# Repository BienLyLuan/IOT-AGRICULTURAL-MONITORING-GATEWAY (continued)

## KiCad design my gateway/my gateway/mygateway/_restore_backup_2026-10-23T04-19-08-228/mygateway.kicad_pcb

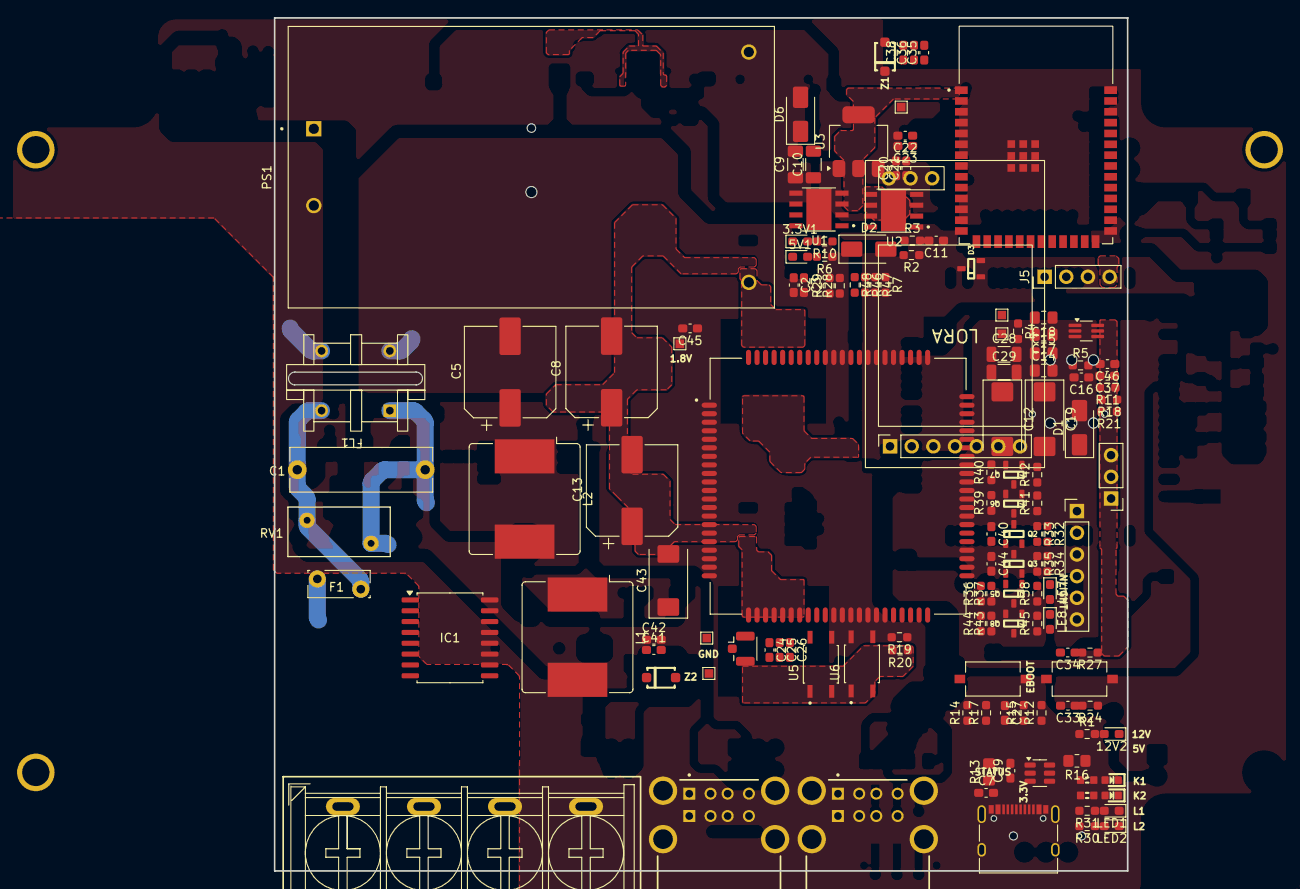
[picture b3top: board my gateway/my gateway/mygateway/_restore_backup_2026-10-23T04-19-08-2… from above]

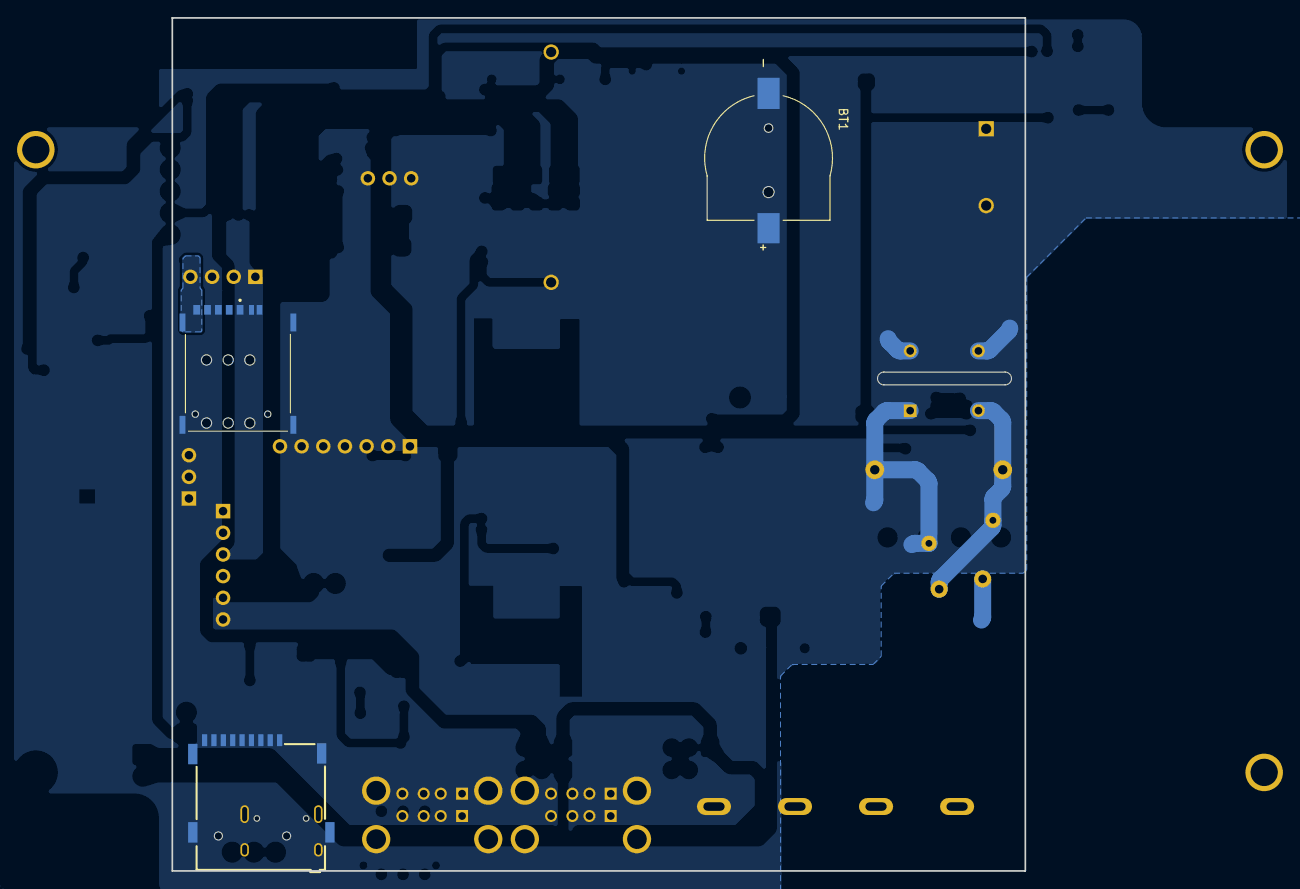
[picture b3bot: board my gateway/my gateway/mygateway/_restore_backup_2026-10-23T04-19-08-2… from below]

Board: 2 copper layers, 100.0 x 100.0 mm, 145 parts (3 on the bottom side), 84 nets.

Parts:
1.8V1, 3.3v2, 4v1, 5v2, 12v1: TestPoint; TestPoint_Pad_1.0x1.0mm
3.3V1, 12V2: Led_red; LED_0603_1608Metric_Pad1.05x0.95mm_HandSolder
5V1: led_red; LED_0603_1608Metric_Pad1.05x0.95mm_HandSolder
BT1: CR1220; MPD_BC501SM-TR
C1: 0.1uF/275VAC; C_Rect_L16.5mm_W5.0mm_P15.00mm_MKT
C2, C7, C21, C22, C25, C33, C35, C39, C42: 10uF/0603; C_0603_1608Metric_Pad1.08x0.95mm_HandSolder
C3, C20, C23, C26, C34, C36, C40, C41, C44, C45, C46: 100nF/0603; C_0603_1608Metric_Pad1.08x0.95mm_HandSolder
C5: 470uF/10x10.5/35V; CP_Elec_10x10.5
C8, C13: 470uF/35V/10x10.5; CP_Elec_10x10.5
C9: 10uF/0805/50V; C_1206_3216Metric_Pad1.33x1.80mm_HandSolder
C10: 100nF/0805/50V; C_1206_3216Metric_Pad1.33x1.80mm_HandSolder
C11, C16: 10nF/0603; C_0603_1608Metric_Pad1.08x0.95mm_HandSolder
C12, C19: 100uF/7343; CP_EIA-7343-31_Kemet-D_Pad2.25x2.55mm_HandSolder
C14: 10uF/1206/50V; C_0805_2012Metric_Pad1.18x1.45mm_HandSolder
C15: 100nF/1206/50V; C_0805_2012Metric_Pad1.18x1.45mm_HandSolder
C17: 100nF/1206; C_0805_2012Metric_Pad1.18x1.45mm_HandSolder
C18: 10uF/1206; C_0805_2012Metric_Pad1.18x1.45mm_HandSolder
C24, C37, C38: 22uF/0603; C_0603_1608Metric_Pad1.08x0.95mm_HandSolder
C27: 100nF; C_0603_1608Metric_Pad1.08x0.95mm_HandSolder
C28: 10uF/0805/50V; C_1206_3216Metric
C29: 100nF/0805/50V; C_1206_3216Metric
C43: 330uF/7343; CP_EIA-7343-31_Kemet-D
D1, D2: SS54/SMA; D_SMA
D3: BAT54C; SOT23-3
D6: SS54; D_SMA
D8: SMF05C; SOT-363_SC-70-6_Handsoldering
EBOOT1: EBOOT; SW_Tactile_SPST_NO_Straight_CK_PTS636Sx25SMTRLFS
ERST1: ERST; SW_Tactile_SPST_NO_Straight_CK_PTS636Sx25SMTRLFS
F1: 500mA; Fuse_Bourns_MF-RG300
FL1: 10mH/UU9.8; ACFilterChoke-UU9.8
GND1: TestPoint; TestPoint_Pad_1.0x1.0mm
H1, H2, H3: MountingHole; MountingHole_3.2mm_M3 Ver2
IC1: RTC_DS3231M; SOIC-16W_7.5x10.3mm_P1.27mm
J1: Screw_Terminal_01x04; TerminalBlock-Vert-THT-4P-P9.5mm-Screw_HB9500 (1)
J2: Screw_Terminal_01x07; lora_module
J3: SD_micro_SIM; SIMCARD
J4: MiSD-PP-9P-V1; MicroSD_Socket_9P
J5: Conn_01x04_Pin; PinHeader_1x04_P2.54mm_Vertical
J7, J8: USBR-A-D-S-O-TH; USB2TANG
J9: Conn_01x06; PinHeader_1x06_P2.54mm_Vertical
J10: USB_C_Receptacle; USB_TypeC_16pin
J11: ANT_LTE; U.FL_Hirose_U.FL-R-SMT-1_Vertical
J15: Conn_01x03_Pin; PinHeader_1x03_P2.54mm_Vertical
L1, L2: 10uH/12x12/Imax7.8A; L_Bourns_SRR1208_12.7x12.7mm
LE7: Netlight; LED_0603_1608Metric_Pad1.05x0.95mm_HandSolder
LE8: Status; LED_0603_1608Metric_Pad1.05x0.95mm_HandSolder
LED1, LED2: Status; LED_0603_1608Metric_Pad1.05x0.95mm_HandSolder
PS1: HLK-20M12
Q2, Q3, Q5, Q8: NPN; SOT23-3
Q6, Q7: SI2300; SOT23-3
R1, R10: 2.2K/0603; R_0603_1608Metric_Pad0.98x0.95mm_HandSolder
R2: 3.3K; R_0603_1608Metric_Pad0.98x0.95mm_HandSolder
R3, R5, R24, R27: 10K; R_0603_1608Metric_Pad0.98x0.95mm_HandSolder
R4: 4.7K; R_0603_1608Metric_Pad0.98x0.95mm_HandSolder
R6, R18, R21, R30, R31, R38, R45: 1K/0603; R_0603_1608Metric_Pad0.98x0.95mm_HandSolder
R7, R46, R47, R48: 33; R_0603_1608Metric_Pad0.98x0.95mm_HandSolder
R11: 1k/0603; R_0603_1608Metric_Pad0.98x0.95mm_HandSolder
R12, R14, R15, R17, R19, R20: 10K/0603; R_0603_1608Metric_Pad0.98x0.95mm_HandSolder
R13, R16: 5.1K; R_0805_2012Metric_Pad1.20x1.40mm_HandSolder
R22, R25: 1K/0603; R_0603
R28, R29, R32, R34, R36, R39, R41, R42, R44: 4.7K/0603; R_0603_1608Metric_Pad0.98x0.95mm_HandSolder
R33, R35, R37, R43: 47K/0603; R_0603_1608Metric_Pad0.98x0.95mm_HandSolder
R40: 4.7KK/0603; R_0603_1608Metric_Pad0.98x0.95mm_HandSolder
RL1, RL2: LED_RED; LED_0603
RV1: 10D561(560V); RV_Disc_D12mm_W5.8mm_P7.5mm
U1, U2: TPS5430DDA; VREG_LM5017MR_NOPB
U3: AMS1117; SOT-223-3_TabPin2
U5, U6: EL357N; OPTO_EL357N-G
U7: e; SIM7600E-H
U8: USBLC6-2P6; SOT-23-6
U9: ESP32-S3-WROOM-1-N4; XCVR_ESP32-S3-WROOM-1-N4
Z1: D_Zener/3.3V; D_SOD-123
Z2: D_Zener 5.1V; D_SOD-123

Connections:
+3.3V: 3.3v2.1 (1_1), C22.1, C23.1, C24.1, C25.1, C26.1, C27.2, C35.1, C36.1, C38.1, IC1.2 (VCC), J4.4 (VDD), J5.2, J8.B01 (VCC2), J9.6, J15.1, LE7.1, LE8.1, R10.1, R11.1, R12.1, R14.1, R15.1, R17.1, R19.1, R20.1, R24.1, R27.1, R28.1, R29.1, R30.2, R31.2, R41.2, R42.2, U3.2 (VO), U9.2 (3V3), Z1.2
+4V: 4v1.1 (1_1), C17.1, C18.1, C19.1, C41.1, C42.1, C43.1, L2.2, R5.2, U7.38 (VBAT), U7.39 (VBAT), U7.62 (VBAT), U7.63 (VBAT), Z2.2
+5V: 5v2.1 (1_1), C2.1, C3.1, C12.1, C20.1, C21.1, C28.1, C29.1, C37.1, D6.2, J2.6, J5.3, J7.A01 (VCC1), J8.A01 (VCC1), L1.2, R3.2, R6.1, R18.1, R21.1, R22.1, R25.1, U3.3 (VI)
+12V: 12v1.1 (1_1), C5.1, C8.1, C9.1, C10.1, C13.1, C14.1, C15.1, PS1.4 (+Vout), R1.1, U1.7 (VIN), U2.7 (VIN)
/Inout/IN1: J7.B02 (D2-), U5.2
/Inout/IN2: J7.B03 (D2+), U6.2
/MCU/D+: J10.A6 (D+), J10.B6 (D+), U8.3
/MCU/D-: J10.A7 (D-), J10.B7 (D-), U8.1
/MCU/EBOOT: C34.1, EBOOT1.1, J9.4, R27.2, U9.27 (IO0)
/MCU/ERST: C33.1, ERST1.1, J9.5, R24.2, U9.3 (EN)
/MCU/USB_D+: U8.4, U9.14 (IO20)
/MCU/USB_D-: U8.6, U9.13 (IO19)
/Module_SIM/MAIN_ANT: J11.1 (In), U7.82 (MAIN_ANT)
/Module_SIM/NETLIGHT: R36.1, U7.51 (NETLIGHT)
/Module_SIM/PWRKEY: C40.1, Q2.3 (C), U7.3 (PWRKEY)
/Module_SIM/RESET: C44.1, Q3.3 (C), U7.4 (RESET)
/Module_SIM/Rx: Q7.2 (S), R40.1, U7.68 (RXD)
/Module_SIM/STATUS: R44.1, U7.49 (STATUS)
/Module_SIM/Tx: Q6.2 (S), R39.1, U7.71 (TXD)
/Module_SIM/USIM_CLK: R47.1, U7.19 (USIM_CLK)
/Module_SIM/USIM_DATA: R48.1, U7.17 (USIM_DATA)
/Module_SIM/USIM_DET: R7.1, U7.53 (USIM_DET)
/Module_SIM/USIM_RST: R46.1, U7.18 (USIM_RST)
/Module_SIM/USIM_VCC: C46.2, D8.4, J3.C1 (VCC), U7.20 (USIM_VDD)
/Module_SIM/VDD_1.8V: 1.8V1.1 (1_1), C45.1, Q6.1 (G), Q7.1 (G), R39.2, R40.2, U7.15 (VDD_1V8)
/Power/FB1: R2.1, R3.1, U1.4 (VSENSE)
/Power/FB2: R4.1, R5.1, U2.4 (VSENSE)
/Power/PH1: C11.2, D2.2, L1.1, U1.8 (PH)
/Power/PH2: C16.2, D1.2, L2.1, U2.8 (PH)
ESP.IN1: R19.2, U5.4, U9.6 (IO6)
ESP.IN2: R20.2, U6.4, U9.7 (IO7)
GND: 3.3V1.2, 5V1.2, 12V2.2, C2.2, C3.2, C5.2, C7.2, C8.2, C9.2, C10.2, C12.2, C13.2, C14.2, C15.2, C17.2, C18.2, C19.2, C20.2, C21.2, C22.2, C23.2, C24.2, C25.2, C26.2, C27.1, C28.2, C29.2, C33.2, C34.2, C35.2, C36.2, C37.2, C38.2, C39.1, C40.2, C41.2, C42.2, C43.2, C44.2, C45.2, C46.1, D1.1, D2.1, D8.2, EBOOT1.2, ERST1.2, GND1.1 (1_1), IC1.5 (GND), IC1.6 (GND), IC1.7 (GND), IC1.8 (GND), IC1.9 (GND), IC1.10 (GND), IC1.11 (GND), IC1.12 (GND), IC1.13 (GND), J2.7, J3.C5 (GND), J3.S (Sheild), J4.6 (VSS), J4.10 (SHIELD), J5.1, J5.4, J7.A04 (GND1), J7.B01 (VCC2), J7.B04 (GND2), J7.S1 (SHIELD), J7.S2 (SHIELD), J7.S3 (SHIELD), J7.S4 (SHIELD), J8.A04 (GND1), J8.B04 (GND2), J8.S1 (SHIELD), J8.S2 (SHIELD), J8.S3 (SHIELD), J8.S4 (SHIELD), J9.1, J10.A1 (GND), J10.A12 (GND), J10.B1 (GND), J10.B12 (GND), J10.S1 (SHIELD), J11.2 (Ext), J15.3, PS1.3 (-Vout), Q2.2 (E), Q3.2 (E), Q5.2 (E), Q8.2 (E), R2.2, R4.2, R13.2, R16.2, R33.1, R35.1, R37.1, R43.1, U1.6 (GND), U1.9 (GNDPAD), U2.6 (GND), U2.9 (GNDPAD), U3.1 (GND), U5.3, U6.3, U7.1 (GND), U7.2 (GND), U7.5 (GND), U7.10 (GND), U7.14 (GND), U7.37 (GND), U7.40 (GND), U7.41 (GND), U7.43 (GND), U7.57 (GND), U7.58 (GND), U7.60 (GND), U7.61 (GND), U7.64 (GND), U7.65 (GND), U7.77 (GND), U7.78 (GND), U7.80 (GND), U7.81 (GND), U8.2, U9.1 (GND), U9.40 (GND), Z1.1, Z2.1
LINE: F1.1, J1.1
LoRa.AUX: J2.5, U9.23 (IO21)
NEUTRAL: C1.2, FL1.1, J1.2, RV1.1
unnamed: 3.3V1.1, R10.2
unnamed: 5V1.1, R6.2
unnamed: 12V2.1, R1.2
unnamed: C1.1, F1.2, FL1.3, RV1.2
unnamed: D3.2, R11.2
unnamed: D8.5, J3.CD, R7.2
unnamed: D3.3, IC1.14 (VBAT)
unnamed: D8.1, J3.C3 (CLK), R47.2
unnamed: D8.3, J3.C7 (I/O), R48.2
unnamed: D8.6, J3.C2 (RST), R46.2
unnamed: J10.A5 (CC1), R13.1
unnamed: J10.B5 (CC2), R16.1
unnamed: J2.1, J2.2, J15.2
unnamed: LE7.2, R38.2
unnamed: LE8.2, R45.2
unnamed: LED1.1, R31.1
unnamed: LED2.1, R30.1
unnamed: FL1.4, PS1.1 (AC/L)
unnamed: FL1.2, PS1.2 (AC/N)
unnamed: Q2.1 (B), R32.2, R33.2
unnamed: Q3.1 (B), R34.2, R35.2
unnamed: Q5.1 (B), R36.2, R37.2
unnamed: Q5.3 (C), R38.1
unnamed: Q8.1 (B), R43.2, R44.2
unnamed: Q8.3 (C), R45.1
unnamed: R18.2, U5.1
unnamed: R21.2, U6.1
unnamed: R22.2, RL2.1
unnamed: R25.2, RL1.1
unnamed: C11.1, U1.1 (BOOT)
unnamed: C16.1, U2.1 (BOOT)
unnamed: LED2.2, U9.24 (IO47)
unnamed: LED1.2, U9.25 (IO48)
Rx0: J8.A03 (D1+), J9.3, U9.36 (RXD0)
Rx.LoRa: J2.4, U9.9 (IO16)
SCL: IC1.16 (SCL), J8.B02 (D2-), R28.2, U9.17 (IO9)
SD.CLK: J4.5 (CLK), U9.20 (IO12)
SD.CS: J4.2 (DAT3/CD), R14.2, U9.18 (IO10)
SD.DET: J4.9 (DET), R12.2, U9.22 (IO14)
SD.MISO: J4.7 (DAT0), R15.2, U9.21 (IO13)
SD.MOSI: J4.3 (CMD), R17.2, U9.19 (IO11)
SDA: IC1.15 (SDA), J8.B03 (D2+), R29.2, U9.12 (IO8)
SIM.Rx1: Q6.3 (D), R41.1, U9.11 (IO18)
SIM.Tx1: Q7.3 (D), R42.1, U9.10 (IO17)
SIM_PWRKEY: R32.1, U9.39 (IO1)
SIM_RESET: R34.1, U9.38 (IO2)
Tx0: J8.A02 (D1-), J9.2, U9.37 (TXD0)
Tx.LoRa: J2.3, U9.8 (IO15)
VBUS: C7.1, C39.2, D6.1, J10.A4 (VBUS), J10.A9 (VBUS), J10.B4 (VBUS), J10.B9 (VBUS), U8.5

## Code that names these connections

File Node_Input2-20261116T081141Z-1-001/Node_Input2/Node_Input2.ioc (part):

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Mcu.Name=STM32F103C(8-B)Tx
Mcu.Package=LQFP48
Mcu.UserName=STM32F103C8Tx
PA1.GPIOParameters=GPIO_Label
PA1.GPIO_Label=EN_RS485
PA1.Signal=GPIO_Output
PA10.Mode=Asynchronous
PA10.Signal=USART1_RX
PA11.GPIOParameters=GPIO_PuPd,GPIO_Label
PA11.GPIO_Label=LORA_AUX
PA11.GPIO_PuPd=GPIO_PULLUP
PA11.Signal=GPIO_Input
PA12.GPIOParameters=GPIO_Label
PA12.GPIO_Label=LORA_EN
PA12.Signal=GPIO_Output
PA13.Mode=Serial_Wire
PA13.Signal=SYS_JTMS-SWDIO
PA14.Mode=Serial_Wire
PA14.Signal=SYS_JTCK-SWCLK
PA2.Mode=Asynchronous
PA2.Signal=USART2_TX
PA3.Mode=Asynchronous
PA3.Signal=USART2_RX
PA4.GPIOParameters=GPIO_Label
PA4.GPIO_Label=DIR
PA4.Signal=GPIO_Output
PA6.Signal=ADCx_IN6
PA8.GPIOParameters=GPIO_Label
PA8.GPIO_Label=LORA_M1
PA8.Signal=GPIO_Output
PA9.Mode=Asynchronous
PA9.Signal=USART1_TX
PB10.Mode=Asynchronous
PB10.Signal=USART3_TX
PB11.Mode=Asynchronous
PB11.Signal=USART3_RX
PB12.GPIOParameters=GPIO_Label
PB12.GPIO_Label=LED_USER
PB12.Signal=GPIO_Output
PB13.GPIOParameters=GPIO_Label
PB13.GPIO_Label=BUZZER
PB13.Signal=GPIO_Output
PB15.GPIOParameters=GPIO_Label
PB15.GPIO_Label=LORA_M0
PB15.Signal=GPIO_Output
PD0-OSC_IN.Mode=HSE-External-Oscillator
PD0-OSC_IN.Signal=RCC_OSC_IN
PD1-OSC_OUT.Mode=HSE-External-Oscillator
PD1-OSC_OUT.Signal=RCC_OSC_OUT
RCC.SYSCLKFreq_VALUE=72000000
RCC.SYSCLKSource=RCC_SYSCLKSOURCE_PLLCLK
board=custom
